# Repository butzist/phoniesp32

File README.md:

# phoniesp32 🎶🔋

A **kid-friendly jukebox** powered by the **ESP32**, inspired by
[Phoniebox](https://phoniebox.de). Unlike the original Raspberry Pi–based
version, **phoniesp32** is designed to be **battery-operated, low-power, and
ultra-portable**.

> ⚠️ Work in Progress — Contributions, ideas, and wiring tips are very welcome!

---

## 📥 Download Latest Firmware

[Download Firmware](https://github.com/butzist/phoniesp32/actions) (download the
`firmware` artifact from the latest run on main)

## ✨ Features

- **ESP32-based jukebox**: replaces the Raspberry Pi with an ESP32-C6.
- **Low-power & battery-ready**: runs on a Li-ion cell with charging and
  buck-boost converter.
- **Bare-metal Rust firmware**: built on the [`embassy`](https://embassy.dev/)
  async embedded framework.
- **Rust-powered Web UI**: implemented with [Dioxus](https://dioxuslabs.com/)
  and served directly from the ESP32.
- **Audio transcoding & upload**: convert music files via the web frontend to
  IMA ADPCM, upload to device, and play back instantly.
- **RFID support**: scan S50 fobs with a MFRC522 module to trigger playlists.
- **Affordable**: target build cost **under 50 CHF**.

---

## 🛠 Components

- **MCU**: ESP32-C6
- **Charging/Power**: BQ24073 (Li-ion charger), TSP631000 (buck-boost converter)
- **Battery**: Li-ion cell (e.g. 18650)
- **Audio**: MAX98357 (I2S DAC + amplifier)
- **Storage**: SD card adapter
- **RFID**: MFRC522 module + S50 RFID fobs

---

## 🏗 Build Options

1. **[DIY Breakout Board Build](./docs/diy-build.md)** - Build using
   off-the-shelf breakout boards on a breadboard or prototype board (~25 CHF)
2. **[PCB Build](./docs/pcb-build.md)** - Build using a compact and robust
   custom PCB board (~30 CHF)
3. **[PCBWay Shared Project](https://www.pcbway.com/project/shareproject/PhoniESP32_v1_2_d32752ab.html)**
   Order PCB on PCBWay with optional partial assembly of basic parts. Tutorial
   TBD

### 🏆 Sponsored by PCBWay

I'm grateful to [PCBWay](https://www.pcbway.com) for sponsoring this project!

The PCB and assembly quality was excellent, and their BOM review caught a few
mistakes I made in component selection — super helpful. I used the sponsorship
to fix minor bugs from v1 (charging indicator) and produce a version that can be
hand soldered. I opted for partial assembly (resistors, capacitors, LEDs) and am
practicing soldering connectors and ICs myself. Update and tutorial TBD — while
waiting, check out my project on PCBWay's shared project platform.

---

## 🚧 Project Status

### Backlog

- [x] Hardware
  - [x] Prototype on breadboard
  - [x] Soldered Prototype
  - [x] Battery charger
  - [x] Schematics
  - [x] Custom PCB
  - [x] Design and 3D print case
- [x] UI (Dioxus)
  - [x] File transcoding
  - [x] Served from device
  - [x] Show last scanned RFID tag ID
  - [x] Switch to Bluma CSS
  - [x] Playback control
  - [x] Store RIFF INFO chunk for artist/title
  - [x] Associate file with RFID tag
  - [x] Configure Wi-Fi settings
  - [x] Playlists
  - [x] List known tags
  - [x] List uploaded files
  - [x] Continue file upload
  - [x] Styling
  - [x] Do not use CDN
  - [x] Update to stable Dioxus 0.7
- [ ] Firmware (Embassy)
  - [x] Fallback to Wi-Fi AP mode
  - [x] Audio pipeline (I2S → MAX98357)
  - [x] SD card access
  - [x] Playback control via buttons
  - [x] Playback control via RFID tags
  - [x] Pause playback
  - [x] Playlists
  - [x] Use RIFF INFO chunk for artist/title
  - [x] Fix concurrent access to file system
  - [x] mDNS responder
  - [x] Turn off Wi-Fi when on battery power
  - [x] Enable Wi-Fi temporarily by pressing volume up+down simultaneously for
        3s
  - [x] Captive portal and DHCP server for WiFi access point
  - [x] Speed up SD access/upload (SD card was bad - turns out cheap SD cards
        are bad at SPI)
  - [ ] Playback control via BLE
  - [x] SD card partitioning support
  - [x] Update to stable esp-hal 1.0
- [x] Web API (picoserve)
  - [x] Associate file with RFID tag
  - [x] Playback control
  - [x] Playback status
  - [x] Last scanned RFID tag ID
  - [x] Configure Wi-Fi settings
  - [x] List known tags
  - [x] List uploaded files
  - [x] Playlists
- [ ] Command line utility
  - [x] Transcode
  - [ ] Upload
  - [ ] Playback control
  - [ ] Associate
- [x] Build system
  - [x] Build and bundle all components
  - [x] Build via GitHub actions
- [ ] Upstream fixes
  - [ ] `dioxus`: Support sass:color.channel()
  - [x] `mfrc522`: async / IRQ support implemented in
        [mfrc522-async](https://github.com/butzist/mfrc522-async)
- [ ] Documentation
  - [x] [API Documentation](./API.md)
  - [x] [DIY Build Instructions](./docs/diy-build.md)
  - [ ] Hand soldering tutorial
  - [ ] Video tutorial

---

## 🤝 Contributing

Want to help build the cheapest, most fun, and hackable jukebox for kids?

- Review my code! I bet there are many possibilities to optimize power/memory
  usage
- Implement any of the missing features
- Share your ideas

PRs, issues, and ideas are always welcome!

---

## 📜 License

MIT License — free to use, hack, and share.

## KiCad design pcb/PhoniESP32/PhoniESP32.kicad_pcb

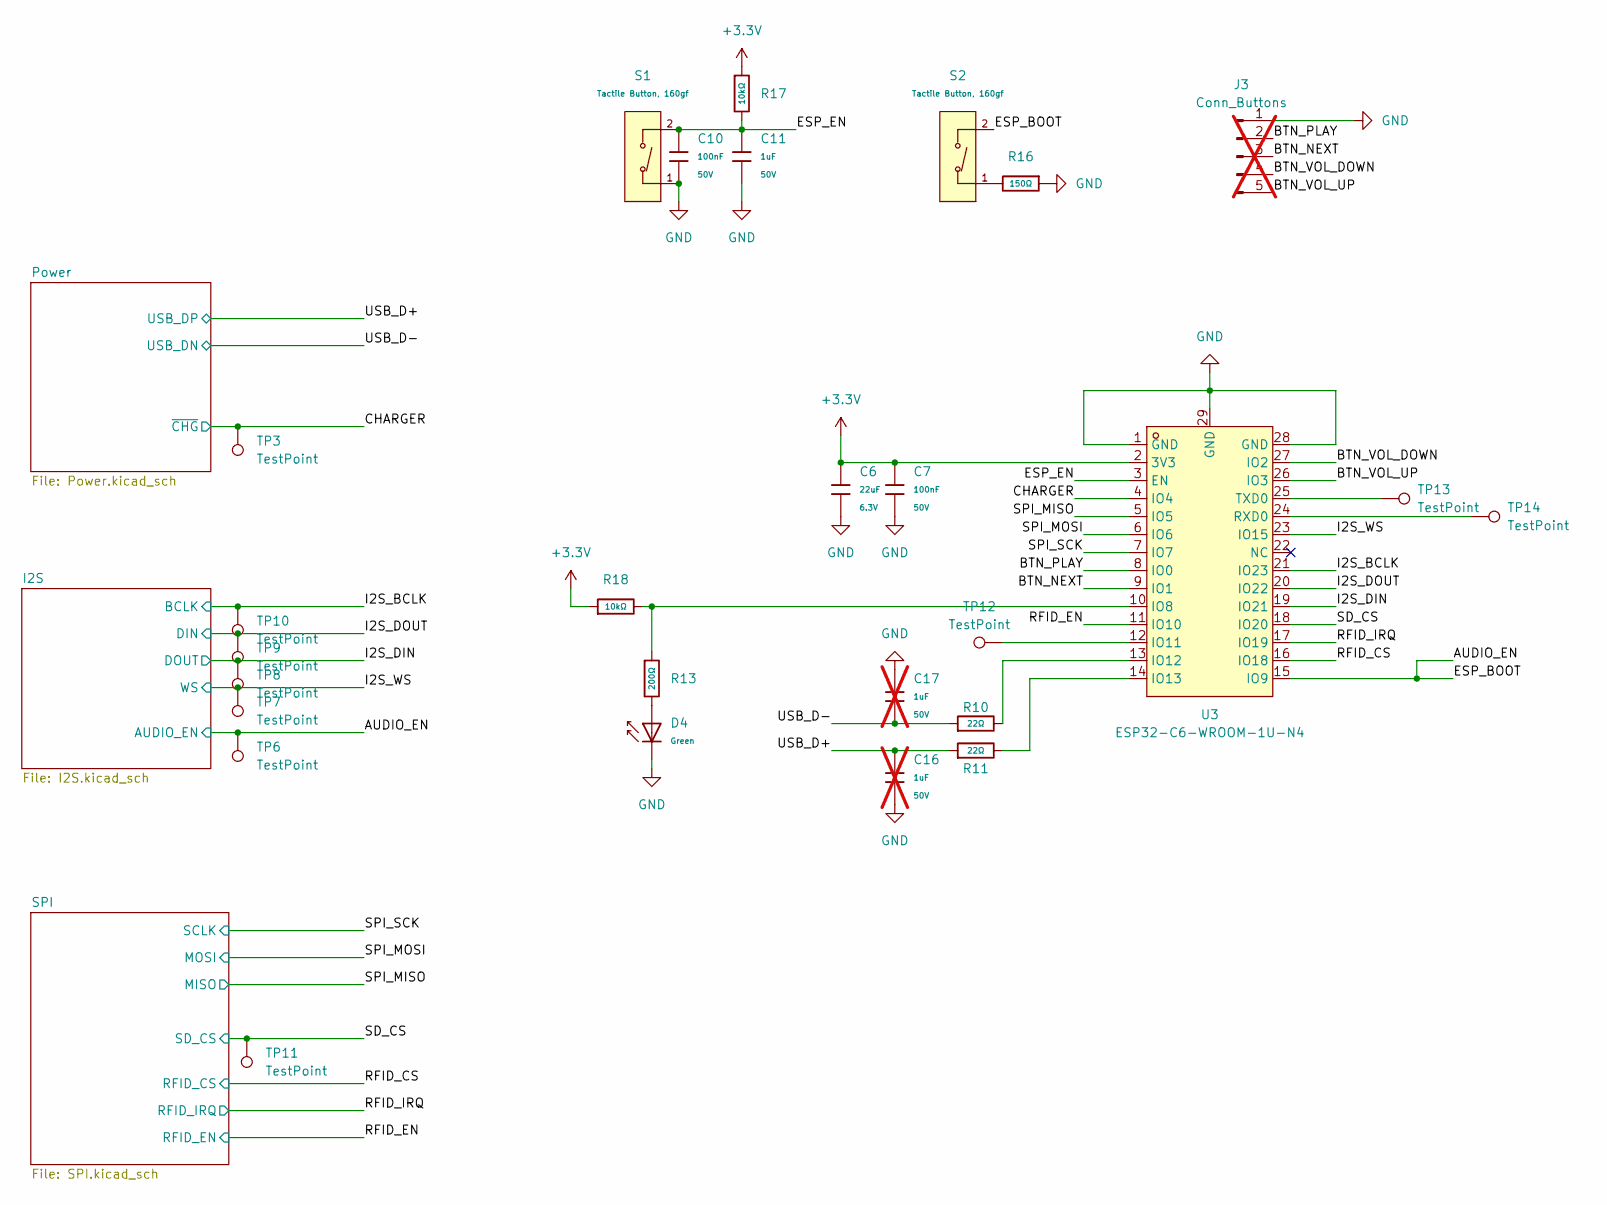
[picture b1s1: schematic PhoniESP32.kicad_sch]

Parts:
C6: 22uF; C_0603; Voltage Rated 6.3V; Tolerance ±20%; Part CL10A226MQ8NRNC; LCSC C59461
C7, C10: 100nF; C_0603; Voltage Rated 50V; Tolerance ±10%; Part CC0603KRX7R9BB104; LCSC C14663
C11: 1uF; C_0603; Voltage Rated 50V; Tolerance ±10%; Part CL10A105KB8NNNC; LCSC C15849
C16, C17: 1uF; C_0603; Voltage Rated 50V; Tolerance ±10%; Part CL10A105KB8NNNC; LCSC C15849; not fitted
D4: Green; D_0805; Part KT-0805G; LCSC C2297
J3: Conn_Buttons; PinHeader_1x05_P2.54mm_Vertical; MPN A2541WV-5P; LCSC Part C225480; not fitted
R10, R11: 22Ω; R_0603; Overload Voltage (Max) 75V; Tolerance ±1%; Part 0603WAF220JT5E; LCSC C23345
R13: 200Ω; R_0603; Overload Voltage (Max) 75V; Tolerance ±1%; Part 0603WAF2000T5E; LCSC C8218
R16: 150Ω; R_0603; Overload Voltage (Max) 75V; Tolerance ±1%; Part 0603WAF1500T5E; LCSC C22808
R17, R18: 10kΩ; R_0603; Overload Voltage (Max) 75V; Tolerance ±1%; Part 0603WAF1002T5E; LCSC C25804
S1, S2: Tactile Button, 160gf; SW_TS-1088-AR02016; Voltage Rating (Dc) 12V; Part TS-1088-AR02016; LCSC C720477
TP3, TP6, TP7, TP8, TP9, TP10, TP11, TP12, TP13, TP14: TestPoint; TestPoint_Pad_D1.0mm
U3: ESP32-C6-WROOM-1U-N4; WIFIM-SMD_28P-L19.2-W18.0-P1.27-TL; MPN ESP32-C6-WROOM-1U-N4; LCSC Part C19272929

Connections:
+3.3V: C6.1, C7.1, R17.1, R18.1, U3.2 (3V3); also elsewhere on the board
/AUDIO_EN: S2.2 (B), TP6.1 (1_1), U3.15 (IO9); also elsewhere on the board
/BTN_NEXT: J3.3, U3.9 (IO1)
/BTN_PLAY: J3.2, U3.8 (IO0)
/BTN_VOL_DOWN: J3.4, U3.27 (IO2)
/BTN_VOL_UP: J3.5, U3.26 (IO3)
/CHARGER: TP3.1 (1_1), U3.4 (IO4); also elsewhere on the board
/ESP_EN: C10.1, C11.1, R17.2, S1.2 (B), U3.3 (EN)
/I2S_BCLK: TP10.1 (1_1), U3.21 (IO23); also elsewhere on the board
/I2S_DIN: TP8.1 (1_1), U3.19 (IO21); also elsewhere on the board
/I2S_DOUT: TP9.1 (1_1), U3.20 (IO22); also elsewhere on the board
/I2S_WS: TP7.1 (1_1), U3.23 (IO15); also elsewhere on the board
/RFID_CS: U3.16 (IO18); also elsewhere on the board
/RFID_EN: U3.11 (IO10); also elsewhere on the board
/RFID_IRQ: U3.17 (IO19); also elsewhere on the board
/SD_CS: TP11.1 (1_1), U3.18 (IO20); also elsewhere on the board
/SPI_MISO: U3.5 (IO5); also elsewhere on the board
/SPI_MOSI: U3.6 (IO6); also elsewhere on the board
/SPI_SCK: U3.7 (IO7); also elsewhere on the board
/USB_D+: C16.1, R11.1; also elsewhere on the board
/USB_D-: C17.1, R10.1; also elsewhere on the board
GND: C6.2, C7.2, C10.2, C11.2, C16.2, C17.2, D4.1, J3.1, R16.1, S1.1 (A), U3.1 (GND), U3.28 (GND), U3.29 (GND); also elsewhere on the board
unnamed: D4.2, R13.2
unnamed: R16.2, S2.1 (A)
unnamed: R13.1, R18.2, U3.10 (IO8)
unnamed: TP12.1 (1_1), U3.12 (IO11)
unnamed: R10.2, U3.13 (IO12)
unnamed: R11.2, U3.14 (IO13)
unnamed: TP14.1 (1_1), U3.24 (RXD0)
unnamed: TP13.1 (1_1), U3.25 (TXD0)

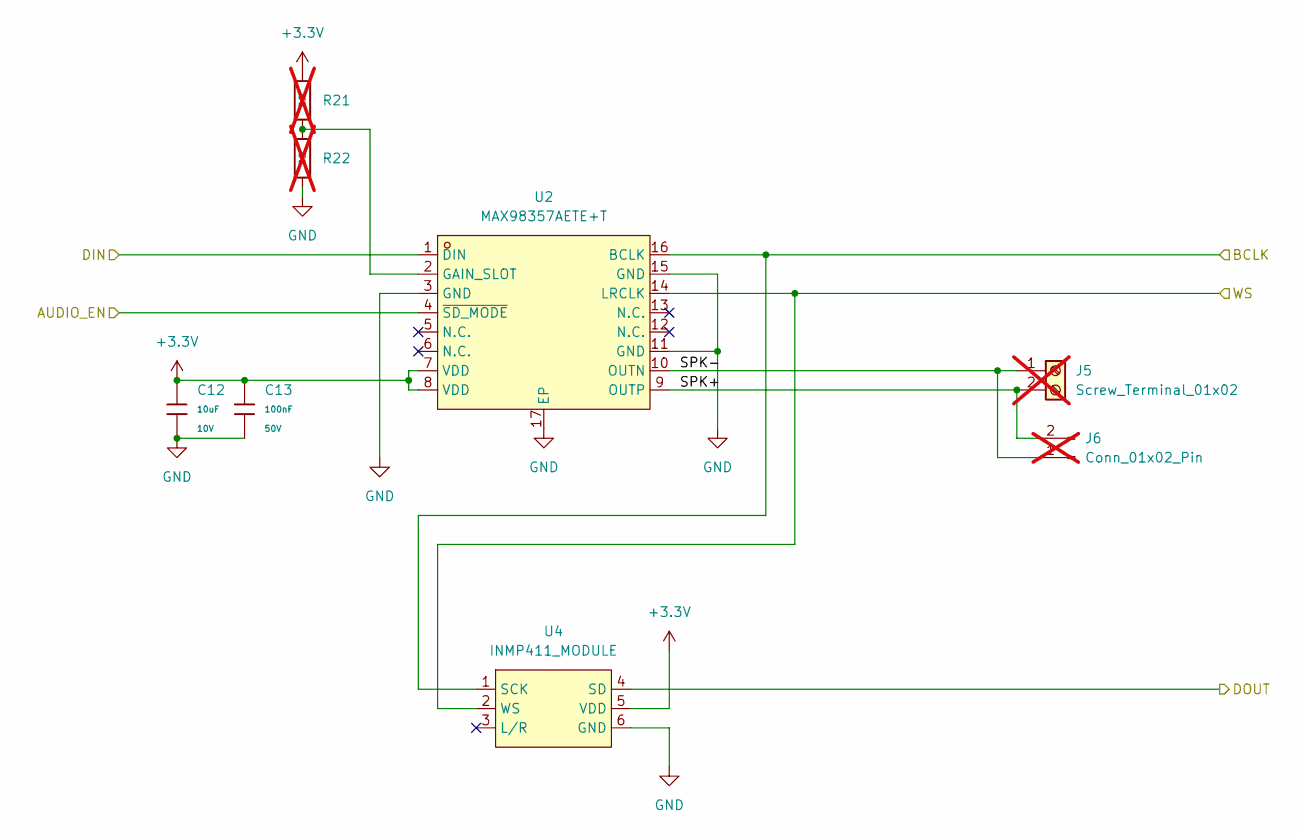
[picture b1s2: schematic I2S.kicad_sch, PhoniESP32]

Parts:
C12: 10uF; C_0603; Voltage Rated 10V; Tolerance ±10%; Part CL10A106KP8NNNC; LCSC C19702
C13: 100nF; C_0603; Voltage Rated 50V; Tolerance ±10%; Part CC0603KRX7R9BB104; LCSC C14663
J5: Screw_Terminal_01x02; TerminalBlock_Xinya_XY308-2.54-2P_1x02_P2.54mm_Horizontal; not fitted
J6: Conn_01x02_Pin; JST_PH_B2B-PH-K_1x02_P2.00mm_Vertical; MPN B2B-PH-K-S(LF)(SN); LCSC Part C131337; not fitted
R21, R22: 0Ω; R_0603; Overload Voltage (Max) 75V; Tolerance ±1%; Part 0603WAF0000T5E; LCSC C21189; not fitted
U2: MAX98357AETE+T; TQFN-16_L3.0-W3.0-P0.50-BL-EP1.5; MPN MAX98357AETE+T; LCSC Part C910544
U4: INMP411_MODULE

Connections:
+3.3V: C12.1, C13.1, R21.1, U2.7 (VDD), U2.8 (VDD), U4.5 (VDD); also elsewhere on the board
/AUDIO_EN: U2.4 (~SD_MODE); also elsewhere on the board
/I2S/SPK+: J5.2, J6.2, U2.9 (OUTP)
/I2S/SPK-: J5.1, J6.1, U2.10 (OUTN)
/I2S_BCLK: U2.16 (BCLK), U4.1 (SCK); also elsewhere on the board
/I2S_DIN: U4.4 (SD); also elsewhere on the board
/I2S_DOUT: U2.1 (DIN); also elsewhere on the board
/I2S_WS: U2.14 (LRCLK), U4.2 (WS); also elsewhere on the board
GND: C12.2, C13.2, R22.2, U2.3 (GND), U2.11 (GND), U2.15 (GND), U2.17 (EP), U4.6 (GND); also elsewhere on the board
unnamed: R21.2, R22.1, U2.2 (GAIN_SLOT)

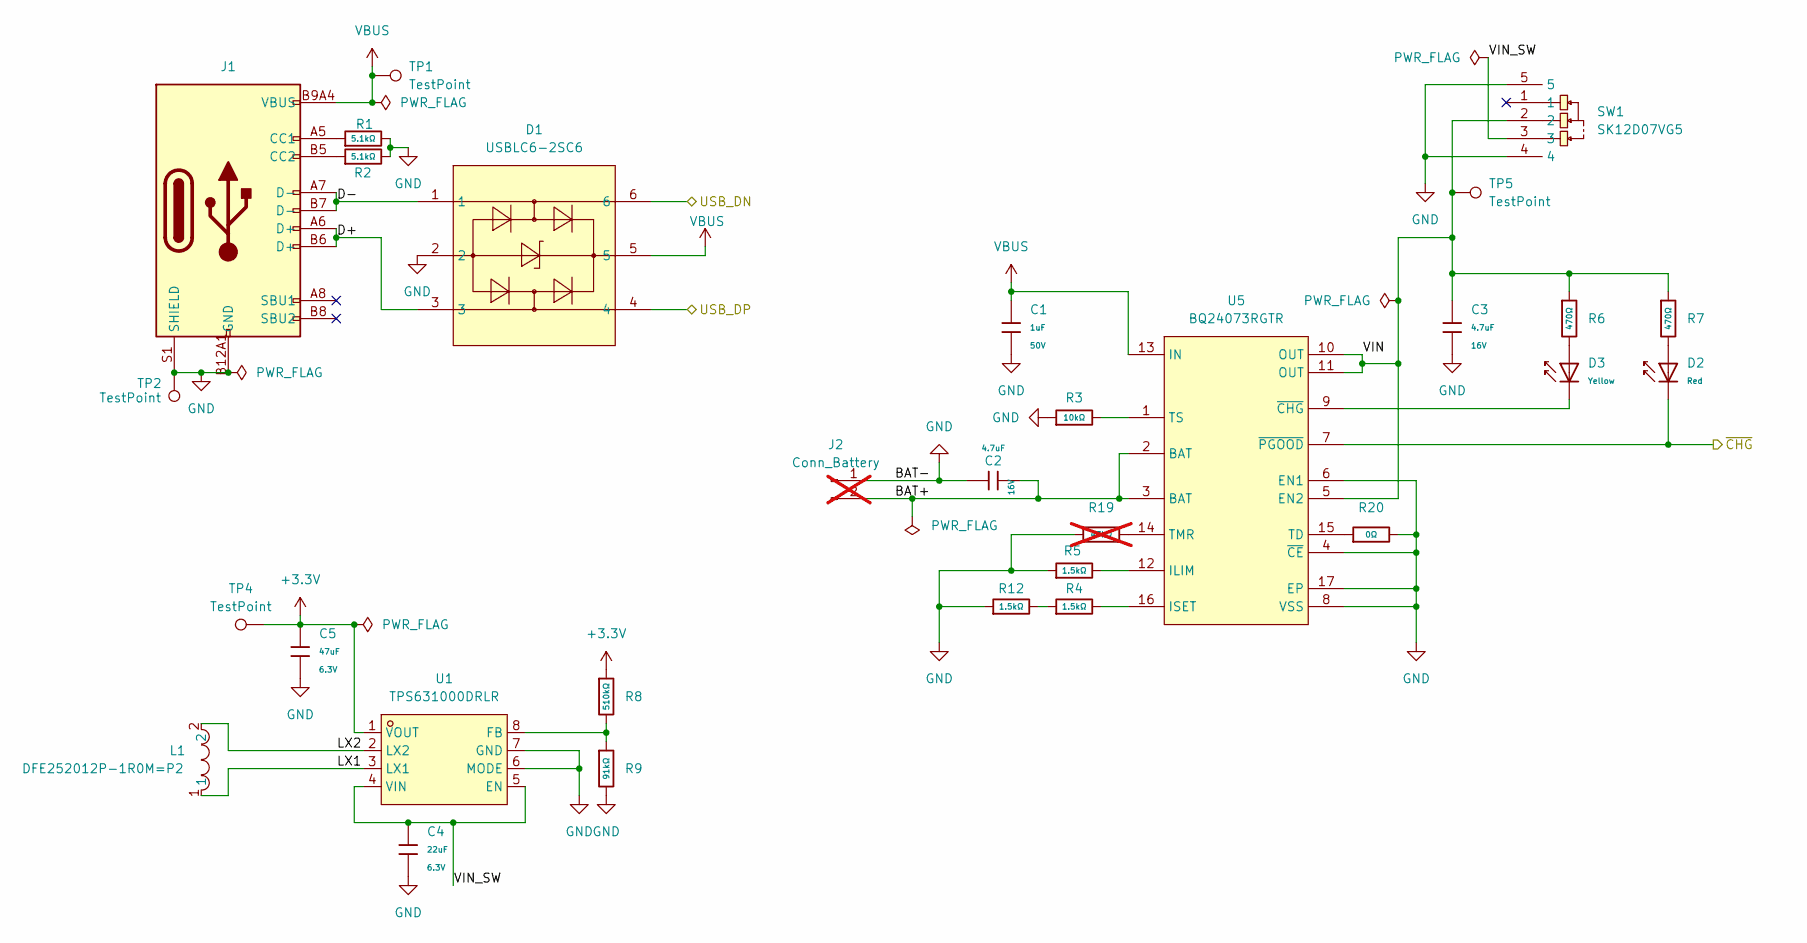
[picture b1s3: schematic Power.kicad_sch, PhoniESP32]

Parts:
C1: 1uF; C_0603; Voltage Rated 50V; Tolerance ±10%; Part CL10A105KB8NNNC; LCSC C15849
C2, C3: 4.7uF; C_0603; Voltage Rated 16V; Tolerance ±10%; Part CL10A475KO8NNNC; LCSC C19666
C4: 22uF; C_0603; Voltage Rated 6.3V; Tolerance ±20%; Part CL10A226MQ8NRNC; LCSC C59461
C5: 47uF; C_0805; Voltage Rated 6.3V; Tolerance ±20%; Part CL21A476MQYNNNE; LCSC C16780
D1: USBLC6-2SC6; SOT-23-6_L2.9-W1.6-P0.95-LS2.8-BL; MPN USBLC6-2SC6; LCSC Part C7519
D2: Red; D_0805; Forward Voltage (VF) 1.6V~2.6V; Part NCD0805R1; LCSC C84256
D3: Yellow; D_0805; Forward Voltage (VF) 1.6V~2.6V; Part KT-0805Y; LCSC C2296
J1: Connector, USB-TYPE-C-16P; TYPE-C-SMD_HX-TYPE-C-16PIN; MPN USB-TYPE-C-019; LCSC C2927039
J2: Conn_Battery; JST_PH_B2B-PH-K_1x02_P2.00mm_Vertical; MPN B2B-PH-K-S(LF)(SN); LCSC Part C131337; not fitted
L1: DFE252012P-1R0M=P2; L1008; MPN DFE252012P-1R0M=P2; LCSC Part C882955
R1, R2: 5.1kΩ; R_0603; Overload Voltage (Max) 75V; Tolerance ±1%; Part 0603WAF5101T5E; LCSC C23186
R3: 10kΩ; R_0603; Overload Voltage (Max) 75V; Tolerance ±1%; Part 0603WAF1002T5E; LCSC C25804
R4, R5, R12: 1.5kΩ; R_0603; Overload Voltage (Max) 75V; Tolerance ±1%; Part 0603WAF1501T5E; LCSC C22843
R6, R7: 470Ω; R_0603; Overload Voltage (Max) 75V; Tolerance ±1%; Part 0603WAF4700T5E; LCSC C23179
R8: 510kΩ; R_0603; Overload Voltage (Max) 75V; Tolerance ±1%; Part 0603WAF5103T5E; LCSC C23192
R9: 91kΩ; R_0603; Overload Voltage (Max) 75V; Tolerance ±1%; Part 0603WAF9102T5E; LCSC C23265
R19: 47kΩ; R_0603; Overload Voltage (Max) 75V; Tolerance ±1%; Part 0603WAF4702T5E; LCSC C25819; not fitted
R20: 0Ω; R_0603; Overload Voltage (Max) 75V; Tolerance ±1%; Part 0603WAF0000T5E; LCSC C21189
SW1: SK12D07VG5; SW-TH_SK12D07VG5-1; MPN SK12D07VG5; LCSC Part C431548
TP1, TP2, TP4, TP5: TestPoint; TestPoint_Pad_D1.0mm
U1: TPS631000DRLR; SOT-583-8_L2.1-W1.2-P0.50-LS1.6-BL; MPN TPS631000DRLR; LCSC Part C5219190
U5: BQ24073RGTR; QFN-16_L3.0-W3.0-P0.50-TL-EP1.7; MPN BQ24073RGTR; LCSC Part C15220

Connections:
+3.3V: C5.1, R8.1, TP4.1 (1_1), U1.1 (VOUT); also elsewhere on the board
/CHARGER: D2.1, U5.7 (~PGOOD); also elsewhere on the board
/Power/BAT+: C2.1, J2.2, U5.2 (BAT), U5.3 (BAT)
/Power/D+: D1.3, J1.A6 (D+), J1.B6 (D+)
/Power/D-: D1.1, J1.A7 (D-), J1.B7 (D-)
/Power/LX1: L1.1, U1.3 (LX1)
/Power/LX2: L1.2, U1.2 (LX2)
/Power/VIN: C3.1, R6.1, R7.1, SW1.2, TP5.1 (1_1), U5.5 (EN2), U5.10 (OUT), U5.11 (OUT)
/Power/VIN_SW: C4.1, SW1.3, U1.4 (VIN), U1.5 (EN)
/USB_D+: D1.4; also elsewhere on the board
/USB_D-: D1.6; also elsewhere on the board
GND: C1.2, C2.2, C3.2, C4.2, C5.2, D1.2, J1.A12B1 (GND), J1.B12A1 (GND), J1.S1 (SHIELD), J2.1, R1.2, R2.2, R3.1, R5.1, R9.2, R12.1, R19.1, R20.2, SW1.4, SW1.5, TP2.1 (1_1), U1.6 (MODE), U1.7 (GND), U5.4 (~CE), U5.6 (EN1), U5.8 (VSS), U5.17 (EP); also elsewhere on the board
unnamed: D2.2, R7.2
unnamed: D3.2, R6.2
unnamed: J1.A5 (CC1), R1.1
unnamed: J1.B5 (CC2), R2.1
unnamed: R4.1, R12.2
unnamed: R8.2, R9.1, U1.8 (FB)
unnamed: R5.2, U5.12 (ILIM)
unnamed: R4.2, U5.16 (ISET)
unnamed: R20.1, U5.15 (TD)
unnamed: R19.2, U5.14 (TMR)
unnamed: R3.2, U5.1 (TS)
unnamed: D3.1, U5.9 (~CHG)
VBUS: C1.1, D1.5, J1.A9B4 (VBUS), J1.B9A4 (VBUS), TP1.1 (1_1), U5.13 (IN)

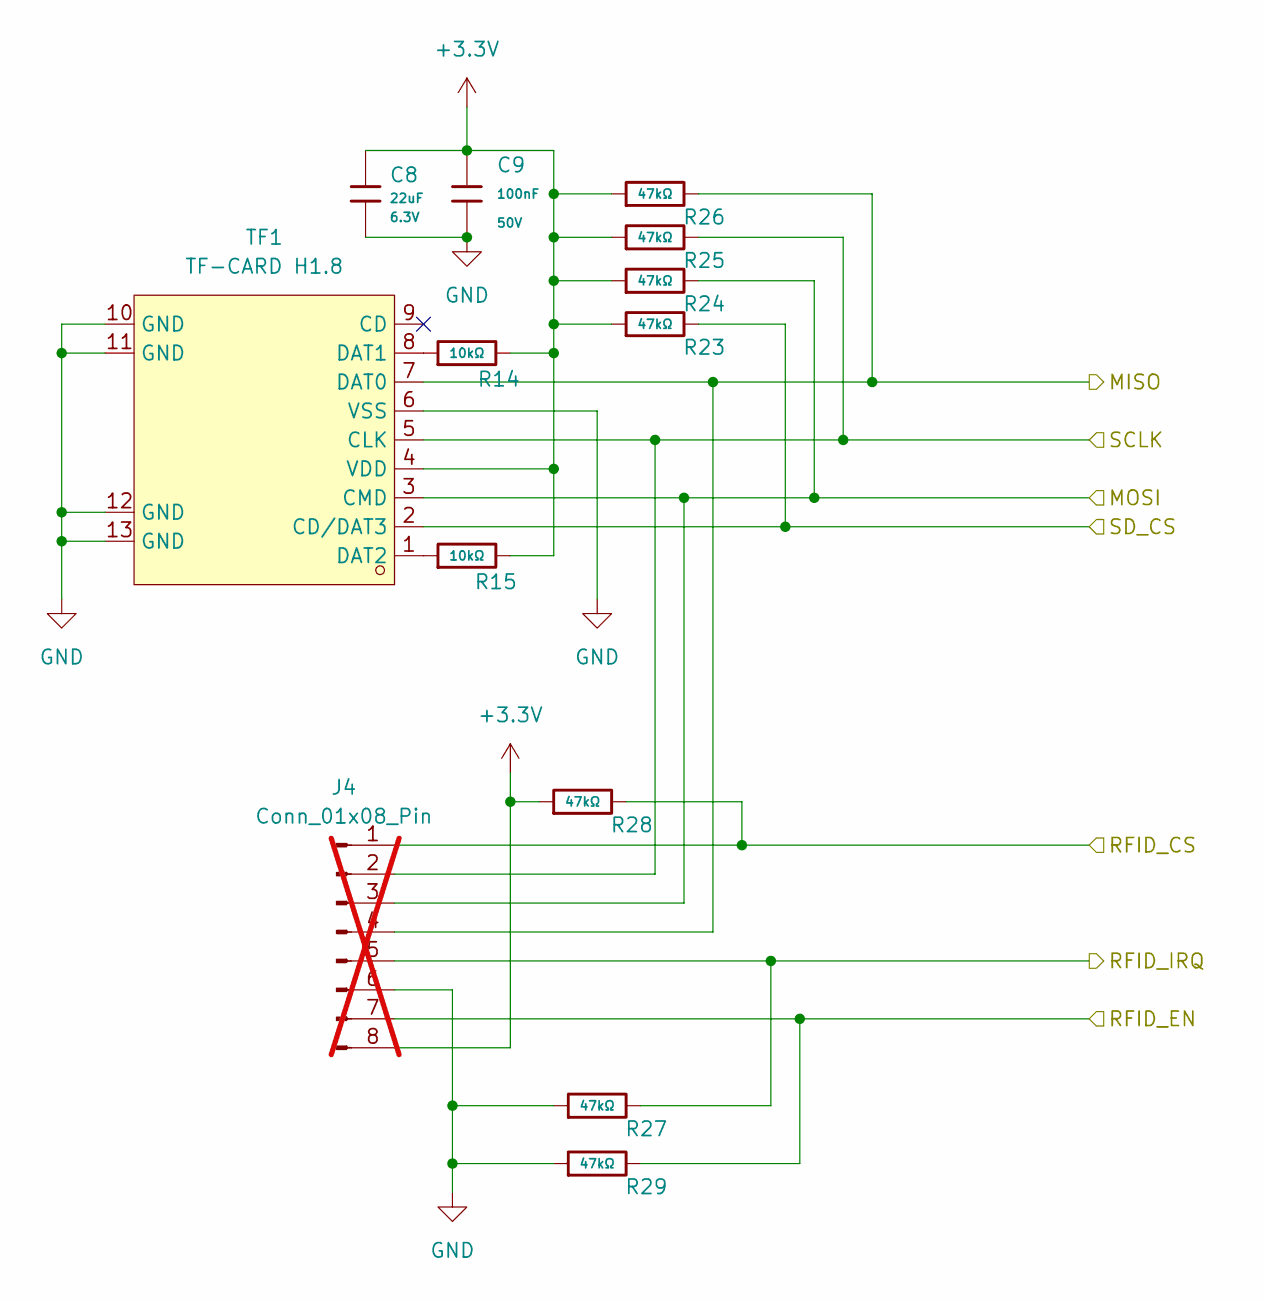
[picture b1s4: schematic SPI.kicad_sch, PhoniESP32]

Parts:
C8: 22uF; C_0603; Voltage Rated 6.3V; Tolerance ±20%; Part CL10A226MQ8NRNC; LCSC C59461
C9: 100nF; C_0603; Voltage Rated 50V; Tolerance ±10%; Part CC0603KRX7R9BB104; LCSC C14663
J4: Conn_01x08_Pin; JST_XH_B8B-XH-A_1x08_P2.50mm_Vertical; MPN B8B-XH-A(LF)(SN); LCSC Part C157972; not fitted
R14, R15: 10kΩ; R_0603; Overload Voltage (Max) 75V; Tolerance ±1%; Part 0603WAF1002T5E; LCSC C25804
R23, R24, R25, R26, R27, R28, R29: 47kΩ; R_0603; Overload Voltage (Max) 75V; Tolerance ±1%; Part 0603WAF4702T5E; LCSC C25819
TF1: TF-CARD H1.8; TF-SMD_TF-CARD-H1.8; MPN TF-CARD H1.8; LCSC Part C7529389

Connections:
+3.3V: C8.1, C9.1, J4.8, R14.2, R15.2, R23.1, R24.1, R25.1, R26.1, R28.1, TF1.4 (VDD); also elsewhere on the board
/RFID_CS: J4.1, R28.2; also elsewhere on the board
/RFID_EN: J4.7, R29.2; also elsewhere on the board
/RFID_IRQ: J4.5, R27.2; also elsewhere on the board
/SD_CS: R23.2, TF1.2 (CD/DAT3); also elsewhere on the board
/SPI_MISO: J4.4, R26.2, TF1.7 (DAT0); also elsewhere on the board
/SPI_MOSI: J4.3, R24.2, TF1.3 (CMD); also elsewhere on the board
/SPI_SCK: J4.2, R25.2, TF1.5 (CLK); also elsewhere on the board
GND: C8.2, C9.2, J4.6, R27.1, R29.1, TF1.6 (VSS), TF1.10 (GND), TF1.11 (GND), TF1.12 (GND), TF1.13 (GND); also elsewhere on the board
unnamed: R14.1, TF1.8 (DAT1)
unnamed: R15.1, TF1.1 (DAT2)

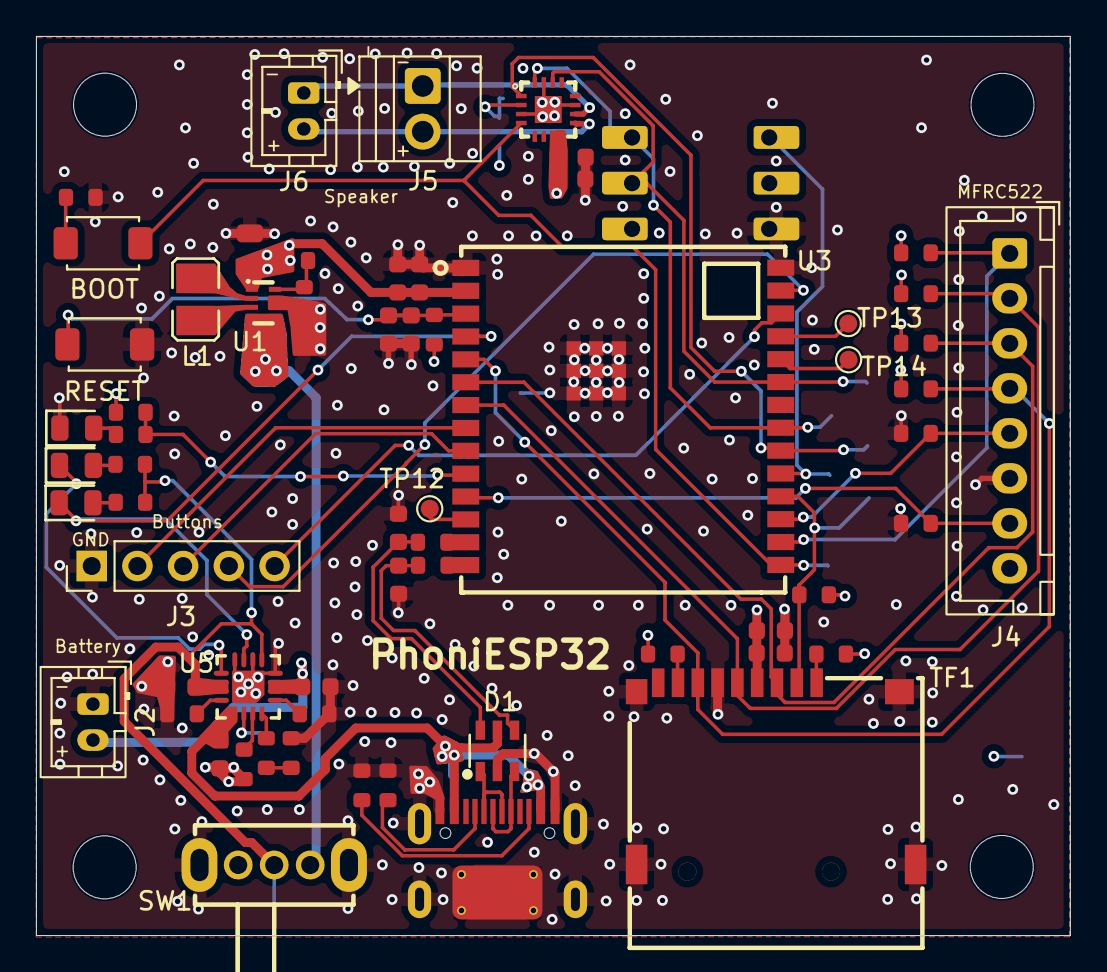
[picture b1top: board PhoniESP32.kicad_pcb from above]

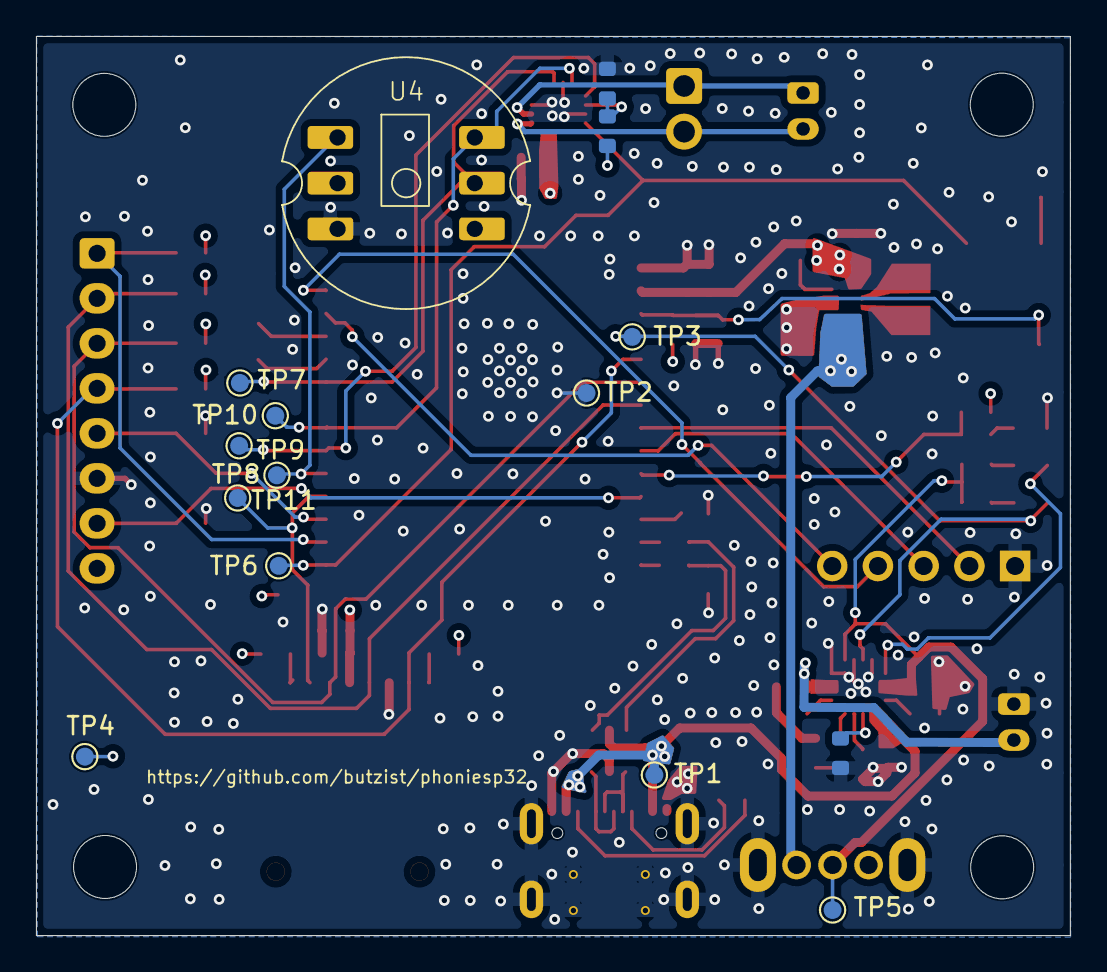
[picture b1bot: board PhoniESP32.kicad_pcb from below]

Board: 4 copper layers, 57.4 x 49.9 mm, 78 parts (15 on the bottom side), 55 nets.

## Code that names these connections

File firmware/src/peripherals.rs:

use esp_hal::gpio::{AnyPin, Level};
use esp_hal::peripherals::DMA_CH0;
use esp_hal::peripherals::DMA_CH1;
use esp_hal::peripherals::I2S0;
use esp_hal::peripherals::LPWR;
use esp_hal::peripherals::SPI2;
use esp_hal::peripherals::SW_INTERRUPT;
use esp_hal::peripherals::TIMG0;
use esp_hal::peripherals::WIFI;

pub struct Peripherals {
    pub spi: SpiPins,
    pub sd_cs: AnyPin<'static>,
    pub rfid_cs: AnyPin<'static>,
    pub rfid_irq: AnyPin<'static>,
    pub rfid_enable: AnyPin<'static>,
    pub audio_enable: Option<(AnyPin<'static>, Level)>,
    pub charger: ChargerPins,
    pub player: PlayerPins,
    pub controls: ControlsPins,

    pub radio: RadioPins,
    pub radio_wifi: WIFI<'static>,
    pub spi_spi2: SPI2<'static>,
    pub spi_dma: DMA_CH1<'static>,
    pub player_i2s: I2S0<'static>,
    pub player_dma: DMA_CH0<'static>,

    pub timer0: TIMG0<'static>,
    pub lpwr: LPWR<'static>,
    pub sw_interrupt: SW_INTERRUPT<'static>,
}

pub struct SpiPins {
    pub sck: AnyPin<'static>,
    pub mosi: AnyPin<'static>,
    pub miso: AnyPin<'static>,
}

pub struct ChargerPins {
    pub pin: AnyPin<'static>,
    pub connected_level: Level,
}

pub struct PlayerPins {
    pub bclk: AnyPin<'static>,
    pub ws: AnyPin<'static>,
    pub dout: AnyPin<'static>,
}

pub struct ControlsPins {
    pub btn_a: AnyPin<'static>,
    pub btn_b: AnyPin<'static>,
    pub btn_c: AnyPin<'static>,
    pub btn_d: AnyPin<'static>,
}

pub struct RadioPins {
    pub pin: AnyPin<'static>,
}

pub fn create_peripherals(peripherals: esp_hal::peripherals::Peripherals) -> Peripherals {
    #[cfg(feature = "pinout_pcb")]
    let is_pcb = true;
    #[cfg(not(feature = "pinout_pcb"))]
    let is_pcb = false;

    let p = peripherals;

    let (spi_sck, spi_mosi, sd_cs, rfid_enable, audio_enable, charger_level) = if is_pcb {
        (
            p.GPIO7.into(),
            p.GPIO6.into(),
            p.GPIO20.into(),
            p.GPIO14.into(),
            Some((p.GPIO9.into(), Level::High)),
            Level::Low,
        )
    } else {
        (
            p.GPIO6.into(),
            p.GPIO7.into(),
            p.GPIO10.into(),
            p.GPIO14.into(),
            None,
            Level::High,
        )
    };

    Peripherals {
        spi: SpiPins {
            sck: spi_sck,
            mosi: spi_mosi,
            miso: p.GPIO5.into(),
        },
        sd_cs,
        rfid_cs: p.GPIO18.into(),
        rfid_irq: p.GPIO19.into(),
        rfid_enable,
        audio_enable,
        charger: ChargerPins {
            pin: p.GPIO4.into(),
            connected_level: charger_level,
        },
        player: PlayerPins {
            bclk: p.GPIO23.into(),
            ws: p.GPIO15.into(),
            dout: p.GPIO22.into(),
        },
        controls: ControlsPins {
            btn_a: p.GPIO0.into(),
            btn_b: p.GPIO1.into(),
            btn_c: p.GPIO2.into(),
            btn_d: p.GPIO3.into(),
        },
        radio: RadioPins {
            pin: p.GPIO8.into(),
        },
        radio_wifi: p.WIFI,
        spi_spi2: p.SPI2,
        spi_dma: p.DMA_CH1,
        player_i2s: p.I2S0,
        player_dma: p.DMA_CH0,
        timer0: p.TIMG0,
        lpwr: p.LPWR,
        sw_interrupt: p.SW_INTERRUPT,
    }
}

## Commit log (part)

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2025-09-29 chore: init
2025-10-03 feat(web): set up web frontend with transcoder in web worker
2025-10-04 feat(transcoder): encode to IMA ADPCM RIFF file
2025-10-04 chore(web): add requests and cleanup
2025-10-08 chore: make basic wifi webserver example work
2025-10-10 feat(wip): read config from SD
2025-10-11 chore(wip): switch to embedded-fatfs (async)
2025-10-11 feat(wifi): add fallback AP
2025-10-12 feat(wip): copy basic rfid reading example
2025-10-12 Revert "feat(wip): copy basic rfid reading example" because is causing interference on i2s
    This reverts commit c66af3195243262b6cdaad84759a3f0e61996aa4.
2025-10-12 chore: update docs
2025-10-14 chore(wip): audio pipeline
2025-10-14 chore(wip): file end handling
2025-10-15 chore(wip): player controls
2025-10-18 chore(wip): try drop and reborrow i2s
2025-10-19 feat(player): audio pipeline
2025-10-19 feat(player): touch controls
2025-10-19 chore: update readme
2025-10-20 chore: cleanup main
2025-10-22 feat: web api
2025-10-23 feat: build automation
2025-10-23 feat: serve website
2025-10-24 chore: disable BLE to free up memory
2025-10-25 chore: disable connection timeouts
2025-10-26 fix: try to fix file writing
2025-10-26 chore: install toolchains locally
2025-10-26 fix: add alternative paths for index.html
2025-10-26 chore: add gh action
2025-10-27 chore(readme): update progress
2025-10-27 fix(firmware): use correct flash/monitor commands
2025-10-28 feat: RFID controls
    This reverts commit 6b5cce0e0bcfc6538ce187b48862e8c22f9d9b72.
2025-10-28 chore(ci): cache nix store/cache
2025-10-28 chore(ci): use cachix
2025-10-28 chore(refactor): extract AudioFile and Playlist entities
2025-10-29 chore: debug
2025-11-08 chore(readme): add updates to stable to todo list
2025-11-08 feat: handle audio metadata
2025-11-08 fix(build): clean firmware.bin
2025-11-08 chore(firmware): switch to upstream embedded-fatfs
2025-11-08 chore(web): update to Dioxus 0.7.1
2025-11-09 feat(web): simple upload and new association pages
2025-11-09 feat(web): simple playback controls + Dioxus Bulma
2025-11-09 fix(audio-file-utils): early exit if LIST section is found
2025-11-09 fix(firmware): compile error in player
2025-11-09 feat(web): refine navbar
2025-11-09 feat(web): wifi settings page
2025-11-09 feat(wip): upload progress
2025-11-09 fix(web): only show loading indicator during file upload
2025-11-09 feat(web): warn if file already exists
2025-11-09 feat(firmware): return metadata for single file
2025-11-10 feat(firmware): stream audio files/associations
2025-11-11 chore(web): proxy /api to device
2025-11-11 fix(web): check if file exists before starting upload
2025-11-16 feat(web): playback status and playlist editor
2025-11-19 feat(web): toast messages
2025-11-19 chore(firmware): update to esp-hal 1.0.0
2025-11-27 fix: chunked upload
2025-11-29 fix: unstable wifi
2025-12-01 chore(transcoder-webworker): integration tests wip
2025-12-01 chore(transcoder): integration tests wip
2025-12-01 fix(web): overwrite files
2025-12-02 chore(ci): run all unit/integration tests
2025-12-02 fix(firmware): synchronized filesystem access
2025-12-03 feat(firmware): mDNS responder
2025-12-04 fix(web): continue upload
2025-12-05 fix(firmware): try to free some memory for stack
2025-12-15 chore(web): inline and customize style
2025-12-15 chore(docs): update README
2025-12-17 chore: compute filename in transcoder
2025-12-17 feat: init CLI utility with transcode
2025-12-18 chore(firmware): enable stack smashing/overflow protection
2025-12-20 feat(wip): power state controls wifi
2025-12-21 chore: wip
2025-12-21 chore(wip): use esp32-c6
2025-12-30 chore(firmware): shared spi bus
2025-12-30 chore(firmware): add script for reporting binary section stats
2026-02-09 fix(firmware): fix justfile for esp32-c6
2026-02-10 chore: debug output during startup
2026-02-10 feat(firmware): use new async mfrc522 driver
2026-02-13 chore(firmware): unify task spawn interfaces
2026-02-13 chore(firmware): encapsulate player controls
2026-02-17 feat(firmware): re-enable controls with long/short press and repeat
2026-02-17 feat(firmware): power state controls wifi
2026-02-17 fix(firmware): debounce key presses
2026-02-18 chore(firmware): run sd card at 20MHz
2026-02-18 chore(firmware): reassign button and power detection pins to allow wakeup from LP
2026-02-22 chore(firmware): reassign pins for easier board layout
2026-02-28 chore(pcb): create schematic - wip
2026-02-28 feat(case): prototype case
2026-02-28 chore(pcb): wip
2026-03-01 chore(pcb): add part libraries
2026-03-01 chore(pcb): add .gitignore
2026-03-01 chore(pcb): power, mcu, spi wip
2026-03-02 feat(pcb): initial schematic
2026-03-02 fix(pcb): add power flags for ERC
2026-03-02 feat(pcb): add power switch
2026-03-02 fix(pcb): add 22 Ohm resistors on USB data lines
2026-03-02 chore(pcb): make charging indicator LEDs brighter
2026-03-03 feat(pcb): initial layout
2026-03-04 feat(pcb): place test points and placeholders
2026-03-04 feat(pcb): initial traces
2026-03-05 chore(pcb): add bigger copper areas for power distribution
2026-03-05 chore(pcb): final cleanups
2026-03-05 chore(pcb): ignore JLCPCB outputs
2026-03-09 fix(transcoder): prevent audio from clipping when normalizing
2026-03-12 fix(pcb): minor revisions by external reviewer
2026-03-12 fix(pcb): resolve via spacing warning
2026-03-13 chore(pcb): switch from PCB antenna to connector
2026-03-18 fix(firmware): config file not written
2026-03-18 chore(firmware): remove debug print during upload
2026-03-20 chore(firmware): update networking
2026-03-20 feat(firmware): captive portal + dhcp server
2026-03-24 chore(docs): DIY build instructions
2026-03-24 feat(firmware): parse SD card partition table
2026-03-26 feat(firmware): add pin mapping for PCB
2026-03-27 chore: remove espup toolchain
2026-03-27 chore: update
2026-04-03 chore(pcb): update to KiCad 10
2026-04-03 fix(pcb): swap pin connector for header
2026-04-15 feat(case): create case
2026-04-15 feat(firmware): disable audio amp when playback stopped
2026-04-15 feat(firmware): disable RFID between scans
2026-04-17 wip(firmware): TLS support
2026-04-17 chore(firmware): remove unnecessary feature flags
2026-04-28 feat(firmware): light sleep between scans when not charging
2026-05-05 feat(pcb): version for hand soldering
2026-05-05 chore(firmware): remove static variable declarations
2026-05-05 fix(firmware): swap volume up/down
2026-05-05 feat(firmware): disable audio amp when paused
2026-05-06 feat(pcb): add labels for basic components
2026-05-10 fix(firmware): wake up from light sleep on button press
2026-06-02 chore(firmware): network controller
2026-06-02 chore(firmware): playback controller
2026-06-02 chore(flake): add jailed opencode
2026-06-02 feat(firmware): WiFi override via volume buttons
2026-06-02 chore(firmware): verbose logging
2026-06-02 fix(firmware): no light sleep if WiFi is active
2026-06-02 fix(firmware): various bugs found during testing
2026-06-02 chore(build/docs): use just recipe options for pinout selection
2026-06-02 fix(firmware): Use RTC to detect WiFi override timeout
2026-06-02 chore(docs): PCB build instructions
2026-06-02 fix(ci): release build
